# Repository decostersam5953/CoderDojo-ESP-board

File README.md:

# CoderDojo-ESP-board
ESP8266 Development board designed for CoderDojo Belgium

# schematic

# board layout

# example

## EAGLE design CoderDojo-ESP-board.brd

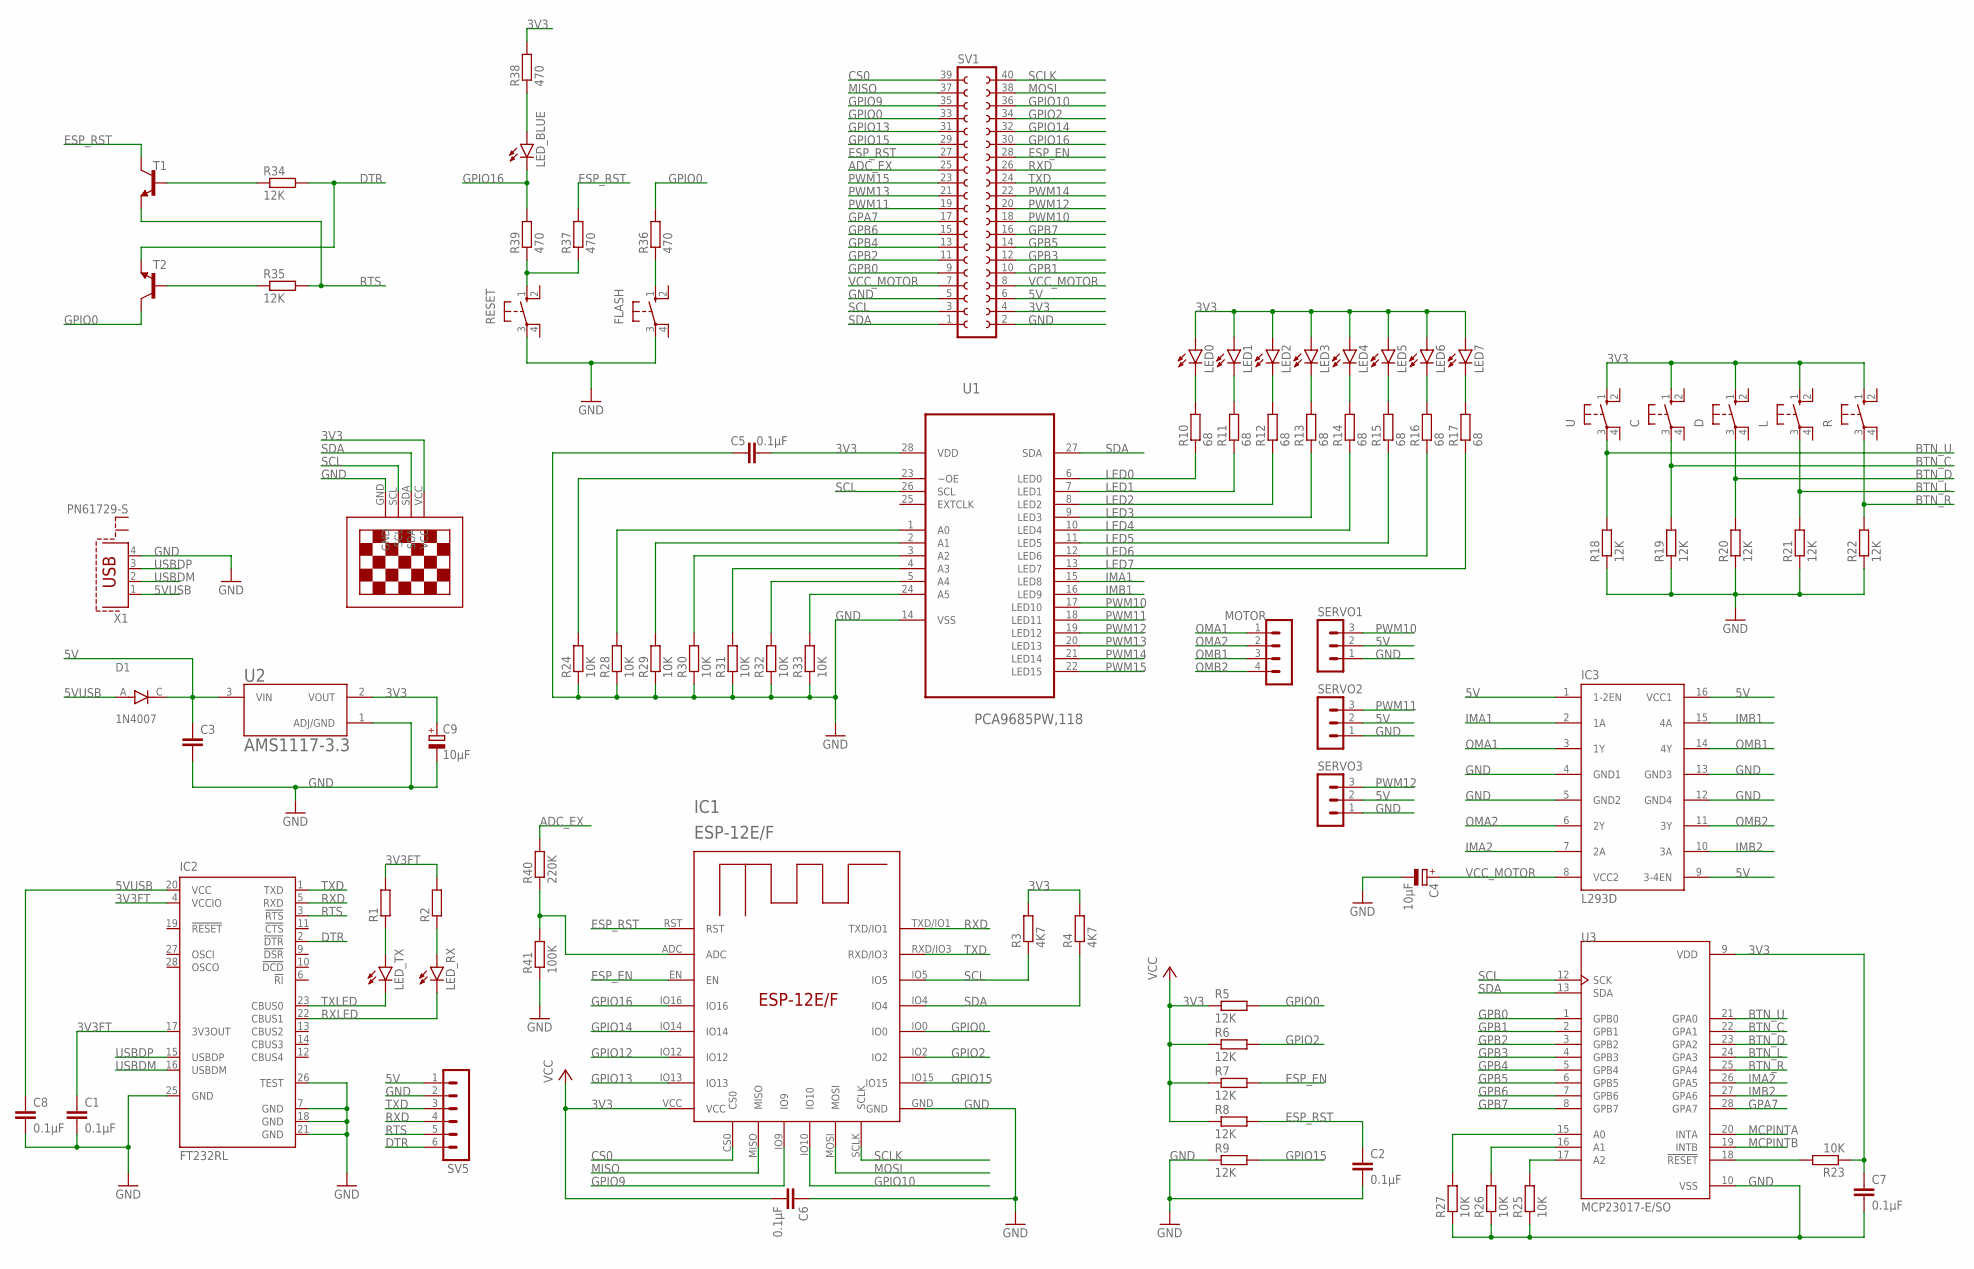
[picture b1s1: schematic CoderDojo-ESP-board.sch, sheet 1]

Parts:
C: 10-XX; B3F-10XX
C1, C2, C5, C6, C7, C8: 0.1µF; C0805
C3: C-EUC0805; C0805
C4, C9: 10µF; E2-5
D: 10-XX; B3F-10XX
D1: 1N4007; DIOAD1060W80L520D270
FLASH: 10-XX; B3F-10XX
IC1: ESP-12E/F; ESP-12E
IC2: FT232RL; SSOP28
IC3: L293D; DIL16
L: 10-XX; B3F-10XX
LED0, LED1, LED2, LED3, LED4, LED5, LED6, LED7: LED3MM
LED_BLUE: LEDSML0805; SML0805
LED_RX: LEDSML0805; SML0805
LED_TX: LEDSML0805; SML0805
MOTOR: MA04-1
R: 10-XX; B3F-10XX
R1, R2: R-EU_R0805; R0805
R3, R4: 4K7; R0805
R5, R6, R7, R8, R9, R18, R19, R20, R21, R22, R34, R35: 12K; R0805
R10, R11, R12, R13, R14, R15, R16, R17: 68; R0805
R23, R24, R25, R26, R27, R28, R29, R30, R31, R32, R33: 10K; R0805
R36, R37, R38, R39: 470; R0805
R40: 220K; R0805
R41: 100K; R0805
RESET: 10-XX; B3F-10XX
SERVO1, SERVO2, SERVO3: MA03-1
SV1: FE20-2
SV5: MA06-1
T1, T2: BC817-40-NPN-SOT23-BEC; SOT23-BEC
U: 10-XX; B3F-10XX
U1: PCA9685PW,118; SOP65P640X110-28N
U2: AMS1117-3.3; SOT229P700X180-4N
U3: MCP23017-E/SO; SOIC127P1030X265-28N
U$1: 13"OLED13"OLED; 1.3"OLED
X1: PN61729-S

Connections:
3V3: C.1 (S), C5.2, C6.2, C7.1, C9.+, D.1 (S), IC1.VCC, L.1 (S), LED0.A, LED1.A, LED2.A, LED3.A, LED4.A, LED5.A, LED6.A, LED7.A, R.1 (S), R3.2, R4.2, R5.1, R6.1, R7.1, R8.1, R23.1, R38.2, SV1.4, U.1 (S), U1.28 (VDD), U2.2 (VOUT), U3.9 (VDD), U$1.VCC
3V3FT: C1.1, IC2.4 (VCCIO), IC2.17 (3V3OUT), R1.2, R2.2
5V: C3.1, D1.C, IC3.1 (1-2EN), IC3.9 (3-4EN), IC3.16 (VCC1), SERVO1.2, SERVO2.2, SERVO3.2, SV1.6, SV5.1, U2.3 (VIN)
5VUSB: C8.1, D1.A, IC2.20 (VCC), X1.1
ADC_EX: R40.2, SV1.25
BTN_C: C.3, R19.2, U3.22 (GPA1)
BTN_D: D.3, R20.2, U3.23 (GPA2)
BTN_L: L.3, R21.2, U3.24 (GPA3)
BTN_R: R.3, R22.2, U3.25 (GPA4)
BTN_U: R18.2, U.3, U3.21 (GPA0)
CS0: IC1.CS0, SV1.39
DTR: IC2.2 (!DTR), R34.2, SV5.6, T2.E
ESP_EN: IC1.EN, R7.2, SV1.28
ESP_RST: C2.1, IC1.RST, R8.2, R37.2, SV1.27, T1.C
GND: C1.2, C2.2, C3.2, C4.-, C5.1, C6.1, C7.2, C8.2, C9.-, FLASH.3, IC1.GND, IC2.7 (GND), IC2.18 (GND), IC2.21 (GND), IC2.25 (GND), IC2.26 (TEST), IC3.4 (GND1), IC3.5 (GND2), IC3.12 (GND4), IC3.13 (GND3), R9.1, R18.1, R19.1, R20.1, R21.1, R22.1, R24.1, R25.1, R26.1, R27.1, R28.1, R29.1, R30.1, R31.1, R32.1, R33.1, R41.1, RESET.3, SERVO1.1, SERVO2.1, SERVO3.1, SV1.2, SV1.5, SV5.2, U1.14 (VSS), U2.1 (ADJ/GND), U3.10 (VSS), U$1.GND, X1.4
GPA7: SV1.17, U3.28 (GPA7)
GPB0: SV1.9, U3.1 (GPB0)
GPB1: SV1.10, U3.2 (GPB1)
GPB2: SV1.11, U3.3 (GPB2)
GPB3: SV1.12, U3.4 (GPB3)
GPB4: SV1.13, U3.5 (GPB4)
GPB5: SV1.14, U3.6 (GPB5)
GPB6: SV1.15, U3.7 (GPB6)
GPB7: SV1.16, U3.8 (GPB7)
GPIO0: IC1.IO0, R5.2, R36.2, SV1.33, T2.C
GPIO2: IC1.IO2, R6.2, SV1.34
GPIO9: IC1.IO9, SV1.35
GPIO10: IC1.IO10, SV1.36
GPIO12: IC1.IO12
GPIO13: IC1.IO13, SV1.31
GPIO14: IC1.IO14, SV1.32
GPIO15: IC1.IO15, R9.2, SV1.29
GPIO16: IC1.IO16, LED_BLUE.C, R39.2, SV1.30
IMA1: IC3.2 (1A), U1.15 (LED8)
IMA2: IC3.7 (2A), U3.26 (GPA5)
IMB1: IC3.15 (4A), U1.16 (LED9)
IMB2: IC3.10 (3A), U3.27 (GPA6)
LED0: R10.1, U1.6 (LED0)
LED1: R11.1, U1.7 (LED1)
LED2: R12.1, U1.8 (LED2)
LED3: R13.1, U1.9 (LED3)
LED4: R14.1, U1.10 (LED4)
LED5: R15.1, U1.11 (LED5)
LED6: R16.1, U1.12 (LED6)
LED7: R17.1, U1.13 (LED7)
MCPINTA: U3.20 (INTA)
MCPINTB: U3.19 (INTB)
MISO: IC1.MISO, SV1.37
MOSI: IC1.MOSI, SV1.38
unnamed: LED_TX.A, R1.1
unnamed: LED_RX.A, R2.1
unnamed: R24.2, U1.23 (~OE)
unnamed: R23.2, U3.18 (!RESET)
unnamed: R28.2, U1.1 (A0)
unnamed: R25.2, U3.17 (A2)
unnamed: IC1.ADC, R40.1, R41.2
unnamed: R26.2, U3.16 (A1)
unnamed: R27.2, U3.15 (A0)
unnamed: R29.2, U1.2 (A1)
unnamed: R30.2, U1.3 (A2)
unnamed: R31.2, U1.4 (A3)
unnamed: R32.2, U1.5 (A4)
unnamed: R33.2, U1.24 (A5)
unnamed: R34.1, T1.B
unnamed: R35.1, T2.B
unnamed: LED0.K (C), R10.2
unnamed: LED1.K (C), R11.2
unnamed: LED2.K (C), R12.2
unnamed: LED3.K (C), R13.2
unnamed: LED4.K (C), R14.2
unnamed: LED5.K (C), R15.2
unnamed: LED6.K (C), R16.2
unnamed: LED7.K (C), R17.2
unnamed: R37.1, R39.1, RESET.1 (S)
unnamed: FLASH.1 (S), R36.1
unnamed: LED_BLUE.A, R38.1
OMA1: IC3.3 (1Y), MOTOR.1
OMA2: IC3.6 (2Y), MOTOR.2
OMB1: IC3.14 (4Y), MOTOR.3
OMB2: IC3.11 (3Y), MOTOR.4
PWM10: SERVO1.3, SV1.18, U1.17 (LED10)
PWM11: SERVO2.3, SV1.19, U1.18 (LED11)
PWM12: SERVO3.3, SV1.20, U1.19 (LED12)
PWM13: SV1.21, U1.20 (LED13)
PWM14: SV1.22, U1.21 (LED14)
PWM15: SV1.23, U1.22 (LED15)
RTS: IC2.3 (!RTS), R35.2, SV5.5, T1.E
RXD: IC1.TXD/IO1, IC2.5 (RXD), SV1.26, SV5.4
RXLED: IC2.22 (CBUS1), LED_RX.C
SCL: IC1.IO5, R3.1, SV1.3, U1.26 (SCL), U3.12 (SCK), U$1.SCL
SCLK: IC1.SCLK, SV1.40
SDA: IC1.IO4, R4.1, SV1.1, U1.27 (SDA), U3.13 (SDA), U$1.SDA
TXD: IC1.RXD/IO3, IC2.1 (TXD), SV1.24, SV5.3
TXLED: IC2.23 (CBUS0), LED_TX.C
USBDM: IC2.16 (USBDM), X1.2
USBDP: IC2.15 (USBDP), X1.3
VCC_MOTOR: C4.+, IC3.8 (VCC2), SV1.7, SV1.8

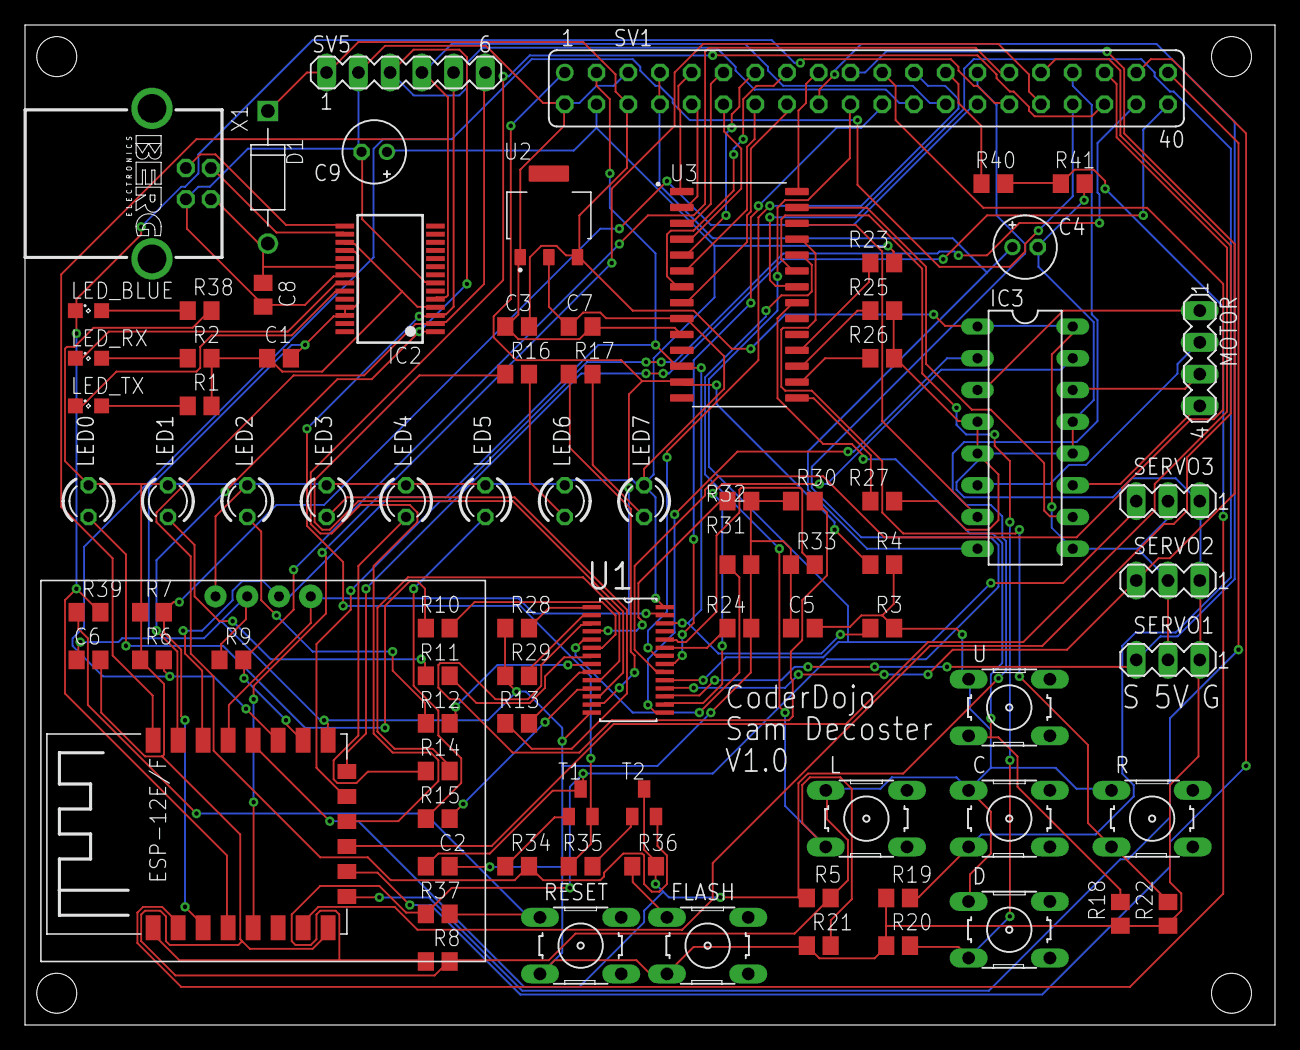
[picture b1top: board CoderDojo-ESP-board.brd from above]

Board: 2 copper layers, 100.0 x 80.0 mm, 85 parts (0 on the bottom side), 94 nets.

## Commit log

2021-12-16 Add datasheets
2021-12-16 Add I2C LCD and ESP library for Eagle
2021-12-16 Add eagle project
2021-12-16 Add schematic
2021-12-19 Add FT232RL to schematic
2021-12-19 Updata schematic
2021-12-19 Add Datasheet AMS1117
2021-12-20 Add PCA9685PW library + add to schematic
2021-12-20 Add LDL1117 datasheet
2021-12-20 Add library of AMS1117-3.3 Voltage regulator
2021-12-20 change AMS1117 library + add to schematic
2021-12-20 add gitignore + add display to schematic
2021-12-20 update gitignore
2021-12-20 Add User buttons
2021-12-20 Add Datasheet 1N4007 Diode
2021-12-20 Add library 1N4007
2021-12-20 Add L293D Motor driver
2021-12-23 Add MCP23017-E/SO package library + update Vdd Vss with correct 3v3/GND
2021-12-30 add BC817 transistor datasheet + update schematic
2021-12-30 add board eagle file
2022-01-02 place components to board + add transistor datasheet S8050
2022-01-04 before routing
2022-01-04 Routing PCB
2022-03-22 Add example images
2022-03-22 udpate
